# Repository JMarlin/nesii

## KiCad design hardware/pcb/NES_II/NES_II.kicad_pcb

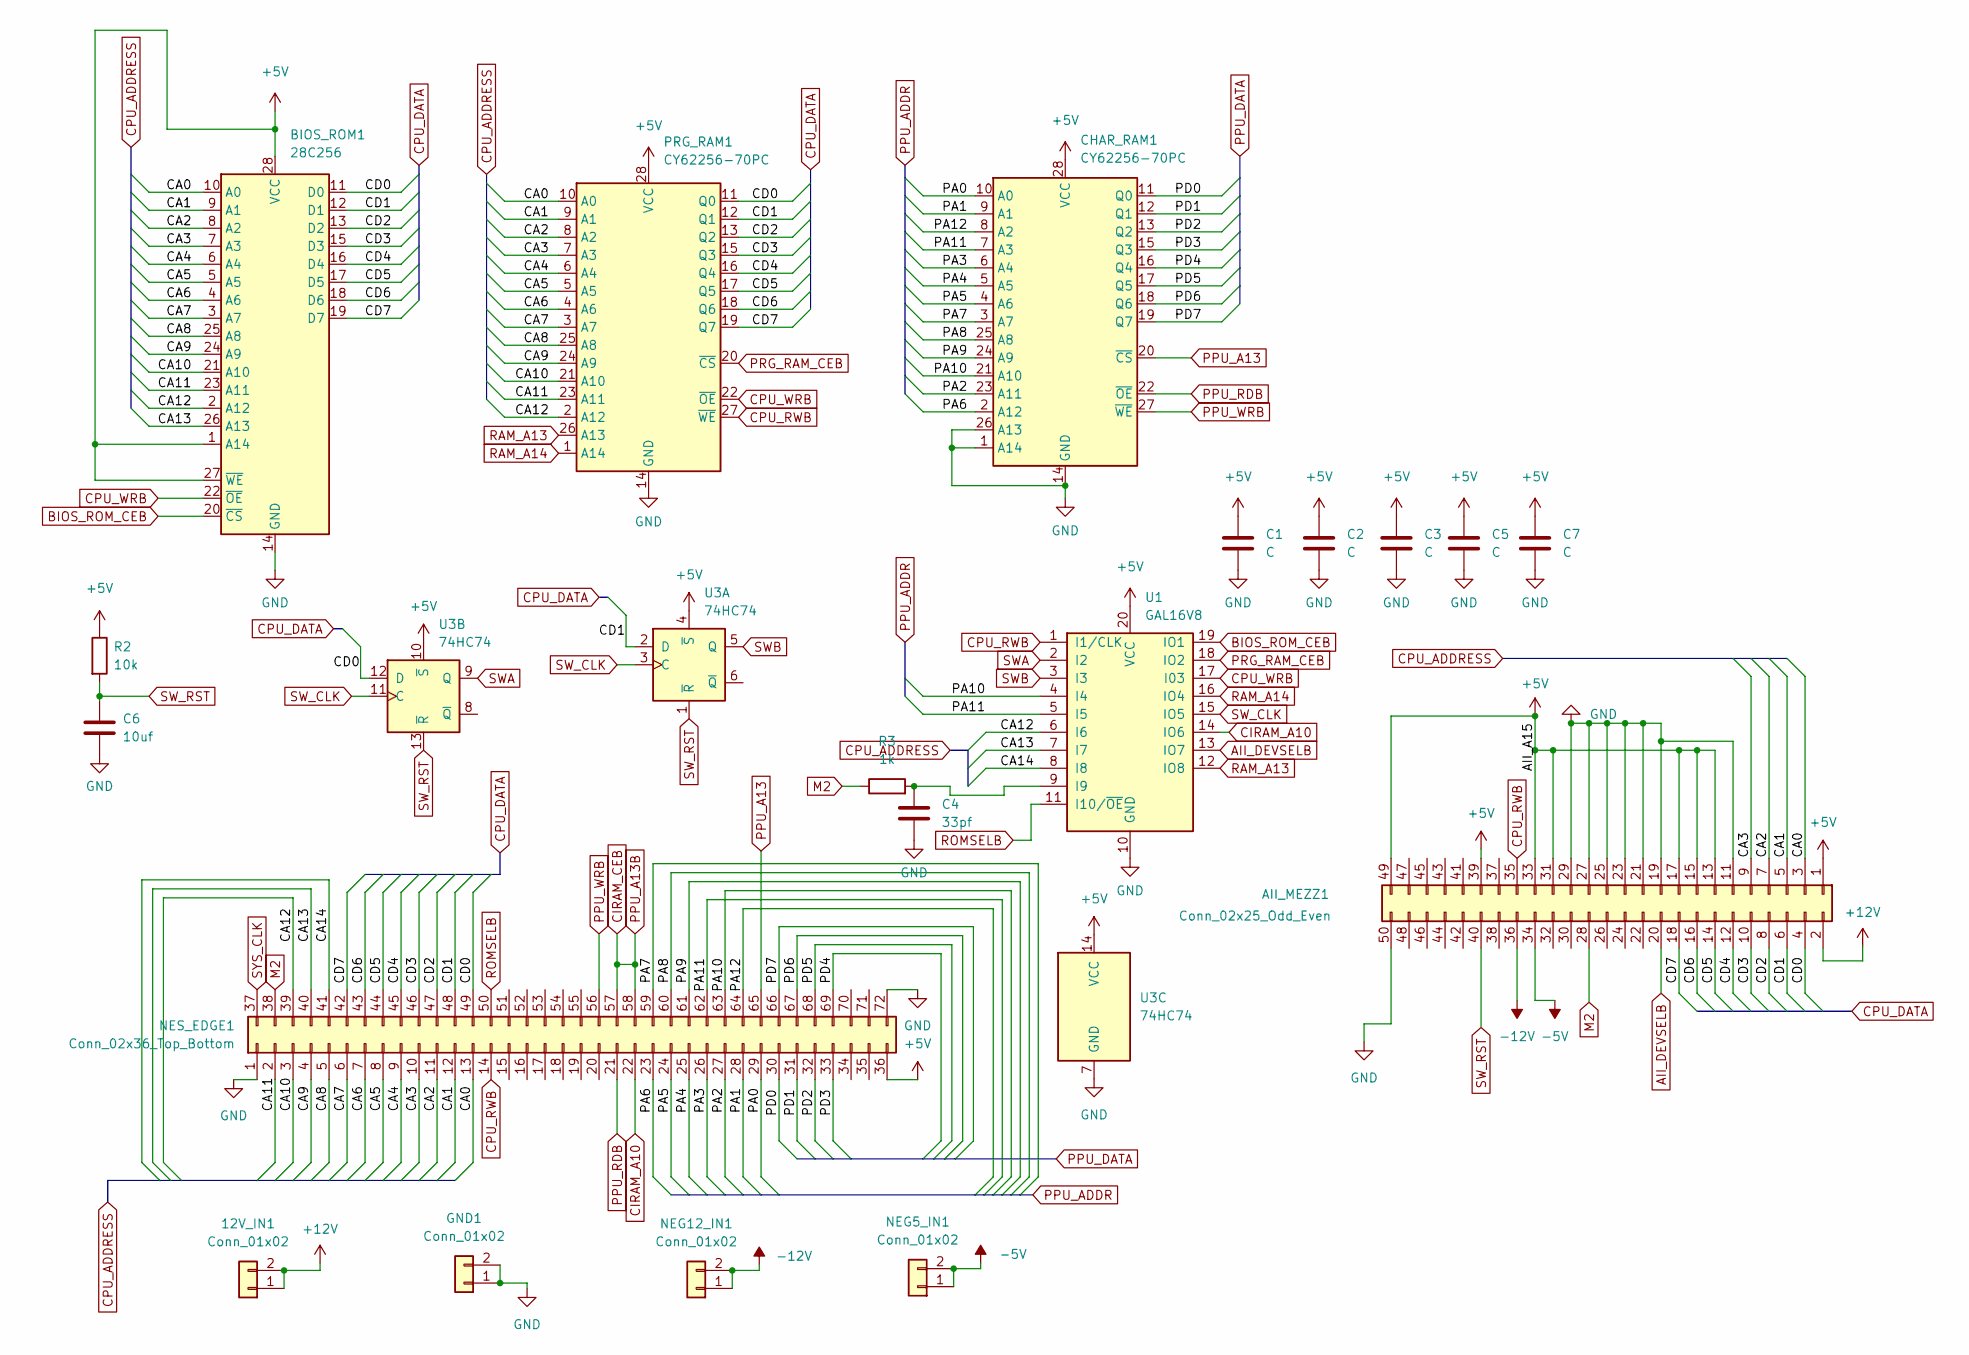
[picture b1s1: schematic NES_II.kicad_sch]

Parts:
12V_IN1: Conn_01x02; PinSocket_1x02_P2.54mm_Vertical
AII_MEZZ1: Conn_02x25_Odd_Even; PinSocket_2x25_P2.54mm_Vertical
BIOS_ROM1: 28C256; DIP-28_W15.24mm_Socket_LongPads
C1, C2, C3, C5, C7: C; CP_Radial_Tantal_D4.5mm_P2.50mm
C4: 33pf; CP_Radial_Tantal_D4.5mm_P2.50mm
C6: 10uf; C_Disc_D3.8mm_W2.6mm_P2.50mm
CHAR_RAM1: CY62256-70PC; DIP-28_W15.24mm_LongPads
GND1: Conn_01x02; PinSocket_1x02_P2.54mm_Vertical
NEG5_IN1, NEG12_IN1: Conn_01x02; PinSocket_1x02_P2.54mm_Vertical
NES_EDGE1: Conn_02x36_Top_Bottom; NES_CART
PRG_RAM1: CY62256-70PC; DIP-28_W15.24mm_LongPads
R2: 10k; R_Axial_DIN0204_L3.6mm_D1.6mm_P5.08mm_Vertical
R3: 1k; R_Axial_DIN0204_L3.6mm_D1.6mm_P5.08mm_Horizontal
U1: GAL16V8; DIP-20_W7.62mm_Socket_LongPads
U3: 74HC74; DIP-14_W7.62mm

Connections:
+5V: AII_MEZZ1.1, AII_MEZZ1.13, AII_MEZZ1.15, AII_MEZZ1.17, AII_MEZZ1.31, AII_MEZZ1.33, AII_MEZZ1.39, AII_MEZZ1.49, BIOS_ROM1.1 (A14), BIOS_ROM1.27 (~WE), BIOS_ROM1.28 (VCC), C1.1, C2.1, C3.1, C5.1, C7.1, CHAR_RAM1.28 (VCC), NES_EDGE1.36, PRG_RAM1.28 (VCC), R2.1, U1.20 (VCC), U3.4 (~S), U3.10 (~S), U3.14 (VCC)
+12V: 12V_IN1.1, 12V_IN1.2, AII_MEZZ1.2
-5V: AII_MEZZ1.34, NEG5_IN1.1, NEG5_IN1.2
-12V: AII_MEZZ1.36, NEG12_IN1.1, NEG12_IN1.2
/CA0: AII_MEZZ1.3, BIOS_ROM1.10 (A0), NES_EDGE1.13, PRG_RAM1.10 (A0)
/CA1: AII_MEZZ1.5, BIOS_ROM1.9 (A1), NES_EDGE1.12, PRG_RAM1.9 (A1)
/CA2: AII_MEZZ1.7, BIOS_ROM1.8 (A2), NES_EDGE1.11, PRG_RAM1.8 (A2)
/CA3: AII_MEZZ1.9, BIOS_ROM1.7 (A3), NES_EDGE1.10, PRG_RAM1.7 (A3)
/CA4: BIOS_ROM1.6 (A4), NES_EDGE1.9, PRG_RAM1.6 (A4)
/CA5: BIOS_ROM1.5 (A5), NES_EDGE1.8, PRG_RAM1.5 (A5)
/CA6: BIOS_ROM1.4 (A6), NES_EDGE1.7, PRG_RAM1.4 (A6)
/CA7: BIOS_ROM1.3 (A7), NES_EDGE1.6, PRG_RAM1.3 (A7)
/CA8: BIOS_ROM1.25 (A8), NES_EDGE1.5, PRG_RAM1.25 (A8)
/CA9: BIOS_ROM1.24 (A9), NES_EDGE1.4, PRG_RAM1.24 (A9)
/CA10: BIOS_ROM1.21 (A10), NES_EDGE1.3, PRG_RAM1.21 (A10)
/CA11: BIOS_ROM1.23 (A11), NES_EDGE1.2, PRG_RAM1.23 (A11)
/CA12: BIOS_ROM1.2 (A12), NES_EDGE1.39, PRG_RAM1.2 (A12), U1.6 (I6)
/CA13: BIOS_ROM1.26 (A13), NES_EDGE1.40, U1.7 (I7)
/CA14: NES_EDGE1.41, U1.8 (I8)
/CD0: AII_MEZZ1.4, BIOS_ROM1.11 (D0), NES_EDGE1.49, PRG_RAM1.11 (Q0), U3.12 (D)
/CD1: AII_MEZZ1.6, BIOS_ROM1.12 (D1), NES_EDGE1.48, PRG_RAM1.12 (Q1), U3.2 (D)
/CD2: AII_MEZZ1.8, BIOS_ROM1.13 (D2), NES_EDGE1.47, PRG_RAM1.13 (Q2)
/CD3: AII_MEZZ1.10, BIOS_ROM1.15 (D3), NES_EDGE1.46, PRG_RAM1.15 (Q3)
/CD4: AII_MEZZ1.12, BIOS_ROM1.16 (D4), NES_EDGE1.45, PRG_RAM1.16 (Q4)
/CD5: AII_MEZZ1.14, BIOS_ROM1.17 (D5), NES_EDGE1.44, PRG_RAM1.17 (Q5)
/CD6: AII_MEZZ1.16, BIOS_ROM1.18 (D6), NES_EDGE1.43, PRG_RAM1.18 (Q6)
/CD7: AII_MEZZ1.18, BIOS_ROM1.19 (D7), NES_EDGE1.42, PRG_RAM1.19 (Q7)
/PA0: CHAR_RAM1.10 (A0), NES_EDGE1.29
/PA1: CHAR_RAM1.9 (A1), NES_EDGE1.28
/PA2: CHAR_RAM1.23 (A11), NES_EDGE1.27
/PA3: CHAR_RAM1.6 (A4), NES_EDGE1.26
/PA4: CHAR_RAM1.5 (A5), NES_EDGE1.25
/PA5: CHAR_RAM1.4 (A6), NES_EDGE1.24
/PA6: CHAR_RAM1.2 (A12), NES_EDGE1.23
/PA7: CHAR_RAM1.3 (A7), NES_EDGE1.59
/PA8: CHAR_RAM1.25 (A8), NES_EDGE1.60
/PA9: CHAR_RAM1.24 (A9), NES_EDGE1.61
/PA10: CHAR_RAM1.21 (A10), NES_EDGE1.63, U1.4 (I4)
/PA11: CHAR_RAM1.7 (A3), NES_EDGE1.62, U1.5 (I5)
/PA12: CHAR_RAM1.8 (A2), NES_EDGE1.64
/PD0: CHAR_RAM1.11 (Q0), NES_EDGE1.30
/PD1: CHAR_RAM1.12 (Q1), NES_EDGE1.31
/PD2: CHAR_RAM1.13 (Q2), NES_EDGE1.32
/PD3: CHAR_RAM1.15 (Q3), NES_EDGE1.33
/PD4: CHAR_RAM1.16 (Q4), NES_EDGE1.69
/PD5: CHAR_RAM1.17 (Q5), NES_EDGE1.68
/PD6: CHAR_RAM1.18 (Q6), NES_EDGE1.67
/PD7: CHAR_RAM1.19 (Q7), NES_EDGE1.66
AII_DEVSELB: AII_MEZZ1.20, U1.13 (IO7)
BIOS_ROM_CEB: BIOS_ROM1.20 (~CS), U1.19 (IO1)
CIRAM_A10: NES_EDGE1.22, U1.14 (IO6)
CIRAM_CEB: NES_EDGE1.57, NES_EDGE1.58
CPU_RWB: AII_MEZZ1.35, NES_EDGE1.14, PRG_RAM1.27 (~WE), U1.1 (I1/CLK)
CPU_WRB: BIOS_ROM1.22 (~OE), PRG_RAM1.22 (~OE), U1.17 (I03)
GND: AII_MEZZ1.11, AII_MEZZ1.19, AII_MEZZ1.21, AII_MEZZ1.23, AII_MEZZ1.25, AII_MEZZ1.27, AII_MEZZ1.29, AII_MEZZ1.50, BIOS_ROM1.14 (GND), C1.2, C2.2, C3.2, C4.2, C5.2, C6.2, C7.2, CHAR_RAM1.1 (A14), CHAR_RAM1.14 (GND), CHAR_RAM1.26 (A13), GND1.1, GND1.2, NES_EDGE1.1, NES_EDGE1.72, PRG_RAM1.14 (GND), U1.10 (GND), U3.7 (GND)
M2: AII_MEZZ1.28, NES_EDGE1.38, R3.1
unnamed: C4.1, R3.2, U1.9 (I9)
PPU_A13: CHAR_RAM1.20 (~CS), NES_EDGE1.65
PPU_RDB: CHAR_RAM1.22 (~OE), NES_EDGE1.21
PPU_WRB: CHAR_RAM1.27 (~WE), NES_EDGE1.56
PRG_RAM_CEB: PRG_RAM1.20 (~CS), U1.18 (IO2)
RAM_A13: PRG_RAM1.26 (A13), U1.12 (IO8)
RAM_A14: PRG_RAM1.1 (A14), U1.16 (IO4)
ROMSELB: NES_EDGE1.50, U1.11 (I10/~OE)
SWA: U1.2 (I2), U3.9 (Q)
SWB: U1.3 (I3), U3.5 (Q)
SW_CLK: U1.15 (IO5), U3.3 (C), U3.11 (C)
SW_RST: AII_MEZZ1.40, C6.1, R2.2, U3.1 (~R), U3.13 (~R)
SYS_CLK: NES_EDGE1.37

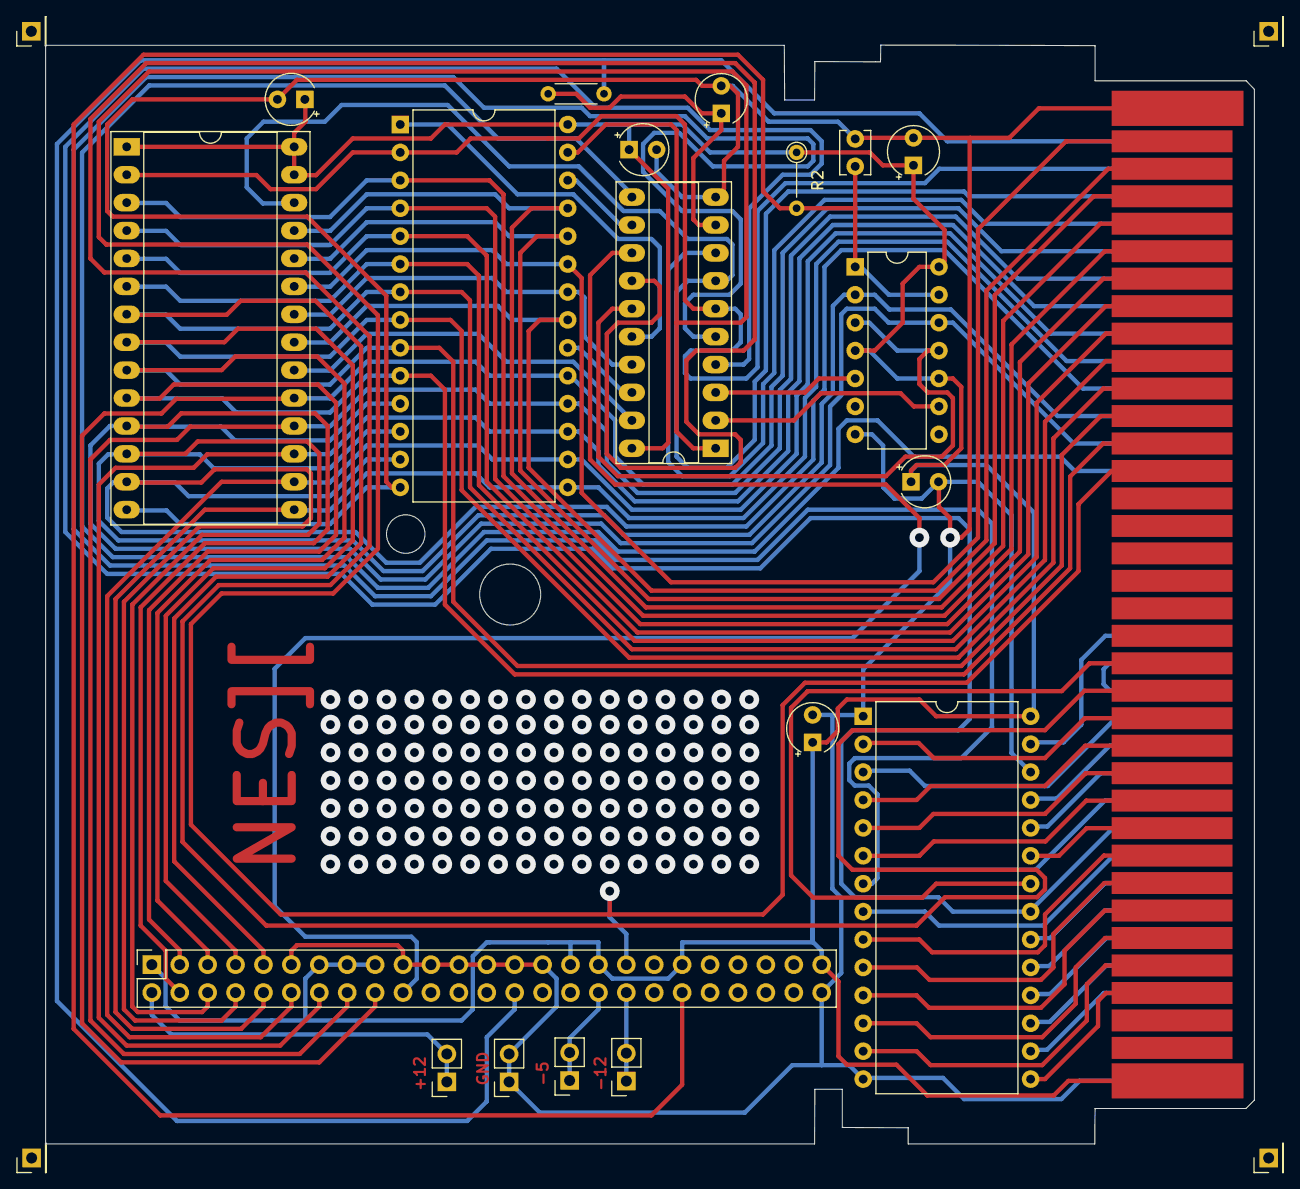
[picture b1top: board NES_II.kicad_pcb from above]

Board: 2 copper layers, 110.0 x 100.0 mm, 20 parts (0 on the bottom side), 68 nets.

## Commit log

2023-09-08 Friday the 8th before VCF @3:15 AM
2024-06-18 #1 figured out how to pack some characters into my available ROM area and get them into CIRAM
2024-06-19 #1 fix line feed
2024-06-19 #1 restore call to init keyboard
2024-06-19 #1 reduce the count of characters cleared in line scrolling
2024-06-20 #3 code successfully halts after disk insertion with a loop checking for an address field
2024-06-20 #3 added Woz ROM track + sector read code, seems to give sane values after early exit
2024-06-21 #3 this copy of the boot ROM successfully and repeatably reads standard-formatted Apple II disks
2024-06-21 #4 set boot rom to jump into disk, create a basic example boot disk image
2024-06-21 #4 -ish, updated ROM and boot disk code to print some dope-ass messages
2024-06-22 Add my sneaky planning for a small modification to the hardware that can enable booting NES games off disk
2024-06-24 First pass of version 2 mapper
2024-06-25 New mapper confirmed working with floppy drive and sram low area swapping
2024-06-26 Working on track seeking in 16k PRG load code, currently able to load from track 0 through track 1 but not on to track 2
2024-06-26 Worked all of the kinks out of head seeking, can now succesfully load the first 16k of data into PRG RAM
2024-06-26 Oh my god, this thing actually runs games
2024-06-26 Made NES disks self-booting
2024-06-26 Added mirroring patching to nes-to-dsk
2024-06-27 Starting work on NOS
2024-06-28 Added a basic framework for a NOS boot image
2024-06-28 Started working on a command processor, definitely doesn't work quite yet
2024-06-29 Basic command processor framework now working properly
2024-06-30 Reorganized NOS into its own directory; Split functional units into their own source files; Implemented enough of the DIR command to seek to and load the VTOC sector
2024-07-01 Fixed disk off after dir command done. Also started trying to implement seek in both directions, which does not currently appear to work
2024-07-02 Doing a test replacing actual floppy seeking with debug printing. Currently bizarrely does many steps in one direction, then many in the other, and then hangs
2024-07-03 #5 fixed arbitrary back/forth seek functionality, should be able to start reading catalog chain now
2024-07-03 #5 roughly printing all catalog entries now. Output needs cleanup
2024-07-03 #5 added disk skewing
2024-07-03 #5 fixed up file name printing starting at wrong offset, still need to figure out why some blank entries are getting printed
2024-07-03 #5 moved vertical margin printing outside of catalog chain loop
2024-07-05 #6 started reorg so that fs layer is built on floppy layer and command layer is built on fs layer
2024-07-06 #7 (because apparently this is actually issue 7, whoops) reorganized the code so that NOS can be compiled into the ROM for rapid development purposes
2024-07-07 #7 implemented dir command as a callback into a fs iterate-files routine for better layering and prepare for iterating file names in run command
2024-07-07 #7 implemented argument handling in command processor and proved it by implementing an echo command
2024-07-08 #7 added stub for implementing run command and fs file lookup, cleaned up nos sources
2024-07-08 #7 finally implemented a prints macro
2024-07-09 #7 find file routine mostly working, needs more testing for space cases
2024-07-10 #7 got T/S sector loaded properly, also moved skewing to the read floppy routine rather than the file scan routine
2024-07-10 #7 implemented print of bin file load address and size, also moved print hex routine out of floppy code and fixed it up
2024-07-11 #7 moved keyboard to second port so that games can use the first port
2024-07-11 Updated to a more readable font
2024-07-12 #7 initial implementation of file open and file read byte
2024-07-12 #7 made sure floppy motor is turned on when read byte needs to grab a fresh sector
2024-07-12 #7 implemented loading of first 256 bytes of binary file
2024-07-15 #7 started restructuring fs routines around an open file info structure
2024-07-17 #7 updated fs sector chain reading, moved floppy conversion table into ROM, testing loading of large files and currently hanging when we get to the 7th data sector for some reason
2024-07-17 #7 found the issue with loading large files, was just another spurious drive turned off too early problem. Can now load a 16k file successfully
2024-07-17 #7 fixed up a small bug in data sector buffer tracking, running binaries tested and confirmed working
2024-07-17 Removed diagnostic messages from run command
2024-07-17 #8 moved floppy.asm over to ROM; NOS and ROM build okay now, but have yet to be tested
2024-07-18 #8 boot sectors moved over to and now build successfully but are untested. Need to finish shell and create a makefile for generating the whole disk image.
2024-07-18 #8 shell application builds, now to assemble and test an actual disk
2024-07-18 #8 boot into the shell is almost working, but there's some kind of really bizarre corruption happening to the loaded shell binary starting at when it's loaded
2024-07-19 #8 solved binary loader issues in system.bin
2024-07-19 #8 loading and running of mario from Apple DOS 3.3 bin files implemented and confirmed working
2024-07-19 Added dk for fun
2024-07-19 #11 move scrolling up to the very last line of the screen
2024-07-20 Massive cleanup and reorg of source tree
2024-07-20 Oh my god, get out of here DS_Store
2024-07-20 Fixup for romemu path
2024-07-20 Helpful note on bios.asm history
2024-07-20 #13 switched from timed wait on the motor to check for data latch change
2024-07-22 #14 motor on timeout implemented
2024-07-23 #14 stashing for the day, code is in absolute disarray. I can get the boot sector to load now, but I can't get it to fail even though it does in the emulator
2024-07-23 #14 fix try-forever in sector header scan by introducing an outer retry counter
2024-07-23 #14 updated NOS makefile to not reverse-skew the boot sectors to match the fact that the bootsector load code also uses skewing now
2024-07-24 #16 display an error message if a NOS disk is booted in an Apple II
2024-07-24 #19 warn and exit if the user tries to run NOS applications on Apple DOS
2024-07-24 Seems about time to bump the feature version again
2024-07-26 #22 added initial copy code and updated cart mapping definitions
2024-07-26 #22 fixed up the PLD and boot plan to match the RAM-bios approach, tested working with copy-to-RAM
2024-07-26 #22 trimmed 3k of space wasted by unused font data
2024-07-26 #22 updated NES launchers, tested working
2024-07-29 22 sram bios (#31)
    * #22 added initial copy code and updated cart mapping definitions
    * #22 fixed up the PLD and boot plan to match the RAM-bios approach, tested working with copy-to-RAM
    * #22 trimmed 3k of space wasted by unused font data
    * #22 updated NES launchers, tested working
    ---------
2024-07-29 #23 scanning for modules seems to work, now need to actually load and init them
2024-07-31 #23 clean up base read sector code and move to floppy routines area
2024-07-31 #23 cleanup of char_io module, has not been checked for compilability
2024-07-31 #23 bios cleanup finished and tested
2024-07-31 #23 work-in-progress on rejiggering the fs read calls to work with the new sector buffering scheme
2024-08-01 #23 updated PLD code to support switches at and extended RAM at , needs code fixup to match
2024-08-06 #23 switching to a mapping version that has low-memory RAM, fixed 4K ROM, and cart peripherals shoved into the last 8K. New floppy location seems to work okay, but normal cart RAM doesn't seem to wor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
2024-08-07 #23 cart RAM wasn't working because I managed to comment out the RAM enable logic
2024-08-07 #23 fix ROM stomping all over switch writes when they're mapped to the same address
2024-08-07 #23 nos now builds and starts to load when using the low memory area, need to finish fixing up the FS code to work with the new sector buffer format so that the shell starts loading properly again
2024-08-30 PCB revision 2
2024-10-28 Add PLD patch for rev 2 hardware
2024-10-29 PLD switches swapped
2024-11-12 #32 fix non-immediate counter load
2024-11-12 #32 fix non-immediate counter load (#33)
2024-11-12 #34 move bios up to - range
2024-11-12 #34 move bios up to - range (#39)
2024-11-12 Initial change, pre-testing
2024-11-12 Initial change, pre-testing (#41)
2024-11-12 #35 initial implementation, ready for testing
2024-11-12 #35 initial implementation, ready for testing (#42)
2024-11-14 #36 hardware and software updated to support write-only switches at
2024-11-14 #36 hardware and software updated to support write-only switches at (#43)
2024-11-20 add msbasic sources
2024-11-20 Removed unnecessary files, added makefile, prepped config file updated memory map
2024-11-21 Created a makefile
2024-11-27 Figured out the bug with the all-zeroes screen, now need to figure out why we're looping at the memory size input
2024-12-01 got as far as the terminal size prompt, but it's currently going right back to memory size prompt after
2025-01-28 Make sure ROM isn't selected if we're writing, closes #40
2025-01-28 Make sure ROM isn't selected if we're writing, closes #40 (#45)
2025-01-28 Successfully implemented and tested slot addressing with MARIO and DONKEY
2025-01-28 Successfully implemented and tested slot addressing with MARIO and DONKEY (#46)
2025-02-01 #38 added RAM CS logic to ensure that the chip is selected always at accesses between and
2025-02-01 #38 added RAM CS logic to ensure that the chip is selected always at accesses between and (#47)
2025-02-01 Add echo to character input
2025-02-01 #27 update ines header blob with proper mapper number
2025-02-06 #27 joojed BASIC load location and RAM base, confirmed working and ready for next steps
2025-02-06 Initial NESII BASIC implementation (#48)
    * add msbasic sources
    * Removed unnecessary files, added makefile, prepped config file updated memory map
    * Created a makefile
    * Figured out the bug with the all-zeroes screen, now need to figure out why we're looping at the memory size input
    * got as far as the terminal size prompt, but it's currently going right back to memory size prompt after
    * Add echo to character input
2025-03-04 #49 add shift mapping table and repurpose zero-page location for shift indication
2025-03-27 #49 implemented PoC write char to screen on NMI code for single character, moved around some header data to more appropriate locations
2025-03-31 #49 vblank-based character print completed
2025-04-01 #49 reduced chrout buffer size to 8 chars because 16 is still too many for vblank on the real NES
2025-04-01 #49 rough non-working skeleton of key scan routine, needs a step-through to make functional
